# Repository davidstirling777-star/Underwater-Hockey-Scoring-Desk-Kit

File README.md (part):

# Underwater Hockey Scoring Desk Kit

A project to allow the use of a computer, modern computer languages, custom printed circuit boards and readily available Arduino or Raspberry Pi 5 hardware to make a scoring and siren system for Underwater Hockey.

**This README is the user manual for the software and hardware assembly.** It combines installation, normal operation, tournament files, two-court results synchronisation, screens, sounds and Zigbee siren setup in one place. The separate `MAINTAINERS.md` is for people modifying the Python source.

The hardware is still being developed but a working prototype has been tested and it does work well. See [Hardware assembly](#hardware-assembly) for the custom control and power PCB build and [`hardware/`](hardware/README.md) for editable KiCad sources for the five custom PCBs you will need to make the system work in totality. [Hardware setup](HARDWARE_SETUP.md) summarises current equipment and commissioning notes; use this README for the assembly wiring.

The software has an operator-facing Underwater Hockey Game Management App and player-facing and/or spectator-facing Display Window(s). The operator window defaults to opening on the **Game Variables** tab, with six other main tabs: **Scoreboard**, **Tournament List**, **Screens**, **Sounds**, **Siren Control**, and **About**.

## Contents

- [How the application works](#how-the-application-works)
- [Hardware assembly](#hardware-assembly)
- [Known working setups](#known-working-setups)
- [Windows 11 installation](#downloading-and-installing-uwh-on-windows)
- [Raspberry Pi 5 installation](#downloading-and-installing-uwh-on-a-raspberry-pi-5)
- [Game Variables tab](#game-variables-tab)
- [Tournament List tab](#tournament-list-tab)
- [Game Sequence](#game-sequence)
- [Two-court tournament results synchronisation](#two-court-tournament-results-synchronisation)
- [Screens tab](#screens-tab)
- [Sounds tab](#sounds-tab)
- [Scoreboard tab](#scoreboard-tab)
- [Other game behaviour](#other-game-behaviour)
- [Zigbee2MQTT wireless siren setup and operation](#zigbee2mqtt-wireless-siren-setup-and-operation)
- [About tab](#about-tab)
- [Other installation and packaging notes](#other-installation-and-packaging-notes)

## How the application works

UWH separates **match setup**, **live match control**, **public display**, **audio**, and **optional wireless control** so the operator can configure a game before play and then work mainly from the Scoreboard tab.

A normal operating flow is:

1. Start UWH and allow the startup self-test to complete.
2. In the **Game Variables** tab, load a preset or enter the match timings and rules.
3. If a tournament draw is being used, use the **Tournament List** tab to select the draw, starting game and any results synchronisation settings.
4. In the **Screens** tab, select the operator layout and open the required player/spectator Display Window(s). Use **Auto Detect Screens** and **Test Displays** when setting up a new computer or monitor arrangement.
5. In the **Sounds** tab, select and test the siren and pip sounds, per-file trims (to ensure the different sounds are balanced or acceptable) and siren timing.
6. If wireless Zigbee referee buttons are being used, configure and test them in the **Siren Control** tab. The wired siren supports Arduino USB and, on Pi 5, GPIO17, independently or together (see [wired siren setup](#wired-siren-on-raspberry-pi-5--gpio17-and-optional-arduino-usb)). Test each connected wired input and check its ON/OFF events in the **Siren Control → Activity Log**.
7. Use the **Scoreboard** tab during the match for goals, penalties, team time-outs and manual timer control. The player/spectator Display Window follows the live match state.
8. At the end of a tournament game, UWH saves the completed result to a separate results CSV before clearing the live match and advancing to the next selected game. If shared two-court sync is enabled, the local save happens first and network upload happens afterwards in the background (Yet to be tested).

The game clock progresses through First Half, Half Time and Second Half, with optional Overtime and Sudden Death when enabled. The detailed sequence and the special rules for goals recorded during breaks are described later in this manual.

## Hardware assembly

The [wireless siren enclosure guide](hardware/Enclosures/UWH_Siren/README.md) includes the printable parts and a photograph of an early working unit. Working units were constructed using grey PLA filament.

The editable KiCad projects and shared libraries are in [`hardware/`](hardware/README.md). These are development hardware sources, not a claim of completed production or thermal certification. The control and power boards as designed for **1 oz copper** as this seems to be significantly cheaper than 2 oz.

The DC-DC PDMs are populated by the PCB manufacturer as they use tiny SMD components, but unless you are will to pay for them to fit the pin header and viable resistor, you will have to solder them yourself.  I could not bring myself to pay the extra.

### Fit only the PDMs you need

**Only fit DC-DC PDM boards for loads that this assembly will power.** The minimum configuration uses **one PDM: the audio supply at power J15**, for a system with the power board, audio board and wired siren. The control circuit receives backed 24 V separately through power J11 → control J21; it does not need another PDM.

- If you supply your own computer instead of the onboard Raspberry Pi 5, omit the Pi PDM at **J18** and its Pi power harness. Use the external computer's audio output (via a 3.5 mm male to male cable between the computer audio socket and the Pool Audio Board 3.5 mm jack) and the Arduino USB pathway for the wired siren.
- If you are going to use the monitors own external power supplies, omit their screen PDMs at **J2/J5/J7/J9** and the corresponding screen-power leads. Fit only as many screen PDMs as there are monitors powered by this assembly.
- Fit the Raspberry Pi PDM only when powering the onboard Raspberry Pi and fit the audio PDM in every configuration described here. Unused PDM positions can remain empty.

### Board stack and assembly order

1. Open each `.kicad_pro` from KiCad's project manager. Install the standard KiCad libraries; the supplied project library tables locate the shared UWH libraries. Refill copper zones and run ERC/DRC before fabrication.
2. Assemble and inspect the power board, DC-DC PDMs and OR-ing board first. Fit the OR-ing module to **power J16**, matching numbered pins and the pin-1 marks; its two-row connector can otherwise be reversed. The supplied 2×5 assignment is SELV on pins 1–2, GND on 3–4 and 7–8, backed output on 5–6, and battery on 9–10. SELV feeds the PDMs controller (a LTC4418) pin V1 and remains the preferred source, even when the battery voltage is higher.
3. Fit only the required PDMs: screen supplies at **J2/J5/J7/J9**, the audio supply at **J15**, and the optional Pi supply at **J18**. Use **DC-DC PDM-Audio Rev D or later for the Pi supply** as eariler versions (which are opaque to you) could not get down to 5V1 required to the Raspberry Pi. **Set and measure outputs** with a multimeter before connecting loads: **19 V** for the specified screens, **16 V nominal and never above 18 V** for audio, and **5.1 V** for the Pi. Verify against each actual load's rating if you can.
4. Fit the components to the Control Board. Fit **both control-board optocouplers U1 and U2**, even if only one controller is used: their input LEDs are in series. Set JP1 **1–2 for Nano ESP32 (3.3 V)** or **2–3 for Nano Every (5 V)** before powering the Arduino. The Pi has its own 3.3 V pull-up through R13.
5. Fit the components to the audio board and the controller hardware required for your configuration: the Pi 5 stack (recommended Pimoroni NVMe Base (you can use a MicroSD at your **increased** risk), active cooler and DAC+), the Arduino, or both, on the upper assembly. Use the matching audio mounting holes.  Do not populate the **audio J5** or **control J10** header unless you are changing the board design. Audio power arrives separately by two wires at audio J19; the mating J5/J10 header still carries the same audio supply and GND, so it is not an electrically isolated mounting connector. So don't fit them.
6. Make the wire harnesses below, check polarity and continuity with power removed, then energise and test one load at a time. Do not connect another USB-C power supply to a Pi already powered through its GPIO header.
7. Mount the **control board above the power board using 30 mm standoffs** at the matching mounting holes. Support the boards without bending them; check screw length and clearance from copper, component leads and the underside of daughterboards. Keep the lower board's terminal-access edge accessible.

### Supply location and wiring sizes

**Suggested 24 V SELV PSU: Mean Well XDR-480E-24.** This model has been tested successfully with the UWH unit and has ample power headroom for the tested configuration.

Locate the **24 V SELV PSU near the 230 V power outlet**, and run several metres of twinned **4 mm² finely multistranded copper cable (approximately AWG 11)**, for 24 V positive and GND, from the PSU to the UWH siren hardware. Check the loaded supply voltage using the procedure below. Keep mains connections at the PSU end. **Containment of the boards to IPX5 is a minimum expectation.**

**24 V supply cable acceptance check:** use **24.0 V nominal at the PSU** and a recommended **maximum 1.0 V drop** from the PSU's DC output terminals to power-board J1 at the highest intended simultaneous load. This is a commissioning target for the supply wiring, **not a verified absolute undervoltage limit for the boards**.

1. With power off, disconnect the backup battery for this test so it cannot mask a weak SELV supply. Connect the equipment that this installation will actually power.
2. Run the connected screens at their highest intended brightness, exercise the computer, and sound the siren at its intended maximum operating level. Use this simultaneous operating load rather than an idle measurement.
3. Set the multimeter to **DC volts**. Measure across the PSU's accessible **+V and −V DC terminals** and record `V_PSU`. At the same steady load, measure across power-board **J1 pin 1 (+24 V) and pin 2 (GND)** and record `V_J1`. Measure only the low-voltage DC side; keep clear of the mains terminals.
4. Calculate **voltage drop = V_PSU − V_J1**. This difference already includes the positive wire, return wire and their connections; do not double it. With **24.0 V measured at the PSU**, the target is **at least 23.0 V at J1**. For example, 24.0 V at the PSU and 23.4 V at J1 gives a **0.6 V drop: pass**. A reading of 22.7 V gives **1.3 V: investigate and correct**.
5. If the PSU itself sags appreciably below its nominal 24 V, investigate its load, adjustment and temperature/derating first. If the cable drop exceeds 1.0 V, power off and inspect the ferrules, terminal tightness and connections; then increase conductor cross-sectional area using compatible, rated terminations. Do not remove strands to fit a terminal or raise the PSU voltage simply to hide cable loss. Repeat the loaded test after correcting it.
6. Confirm that the PDM outputs remain at their required voltages and that startup/siren operation causes no resets, screen blanking or unintended battery takeover. A multimeter's steady reading does not rule out brief dips; investigate any such symptoms even if the steady cable-drop test passes. Reconnect the battery with power off, then test backup operation separately.

Power-board **J1 is Phoenix Contact 1714971**. **4 mm² finely multistranded cable fits the terminals with a bootlace ferrule formed using a ferrule crimper**. Phoenix Contact publishes a **4 mm² maximum for flexible conductors, including ferruled conductors**. Do not trim away strands. Check the actual PSU terminal rating separately. Protect the long cable at its source as appropriate to the cable and PSU; the board fuse cannot protect a short upstream of itself.

Use flexible copper for internal harnesses. The following starting sizes assume maximum internal runs of **up to 250 mm one way**, Use terminations rated for the selected conductor and current. The TB007-508 terminals are specified for up to **2.5 mm²**; GPIO crimp contacts require their own wire-size check.

| Connection | Pin-to-pin wiring | Suggested conductor area, each wire |
|---|---|---|
| PSU to power board | J1 **1 = +24 V**, **2 = GND** | **4 mm² (approx. AWG 11)** |
| 24 V battery to power board | J14 **1 = battery +**, **2 = GND** | **2.5 mm² (approx. AWG 14)**; battery-source protection close to the battery |
| Power board to control board | J11 **1 → J21.1**, **2 → J21.2**: backed 24 V / GND | **0.5 mm² (approx. AWG 20)** for the control circuit only |
| Power board to audio board | J10 **1 → audio J19.1**, **2 → audio J19.2**: audio supply / GND | **1.0 mm² (approx. AWG 17)** |
| Power board to Pi power harness | J17 **1 = +5.1 V**, **2 = GND** | **1.5 mm² (approx. AWG 15)** trunk for each polarity |
| Pi harness branches | +5.1 V to physical **2 and 4**; GND to physical **6 and 9** | Two short **0.5 mm² (approx. AWG 20)** branches per polarity, with suitable current-rated contacts |
| Pi siren signal | Control J19 **1 → Pi physical 11 (BCM GPIO17)** | **0.25 mm² (approx. AWG 24)** |
| Pi pull-up supply | Pi physical **1 (3.3 V) → control J19.2** | **0.25 mm² (approx. AWG 24)** |
| Remote normally open siren button | Across control **J20 pins 1 and 2** | In-use cable: **30 metres of Cat 6a Ethernet patch cable**, plugs cut off, with **four conductors connected in parallel for each leg**, using all eight conductors |

For the remote button cable, join the same group of four conductors together at **both ends** of each leg. Connect one group between **J20 pin 1** and one button terminal, and the other group between **J20 pin 2** and the other button terminal. The normally open button closes the loop when pressed. This cable is used only as button wiring, not as an Ethernet connection.

Wind the 30 metre button cable onto a **spearfishing float-line winder** for tidy storage and easy deployment. The example below is the type used in this setup.

*Example line winder. Product photo: Ocean Hunter.*

Split the Pi power trunk using a rated splice/distribution connection; do not try to force the trunk wire into a small GPIO contact. Use both listed 5 V contacts and both ground contacts. With the DAC+ installed, use a suitable pass-through header/interposer rather than disturbing the HAT connections. An example cable connector is the **Harwin M20-1070600**, a **2×6-position, 2.54 mm female crimp housing**, fitted with separately supplied **M20-1180042** contacts. It can connect the harness to accessible mating pins covering Pi physical pins **1–12**, which include all the power, ground, 3.3 V and GPIO17 connections listed above. The housing is not itself a pass-through interposer: confirm mating-pin length, clearance and pin-1 orientation with the DAC+ fitted, and leave unused positions unwired. The M20-1180042 contacts accept **0.05–0.33 mm² (30–22 AWG)** wire, so the table's **0.5 mm² (approximately AWG 20)** power branches cannot be crimped directly into them. For this connector, use short **0.33 mm² (22 AWG)** power tails from rated splices, retaining both 5 V and both GND contacts, and verify voltage drop and temperature at the intended load. Measure 5 V at the Pi under load; do not compensate for excessive cable loss by raising the PDM above 5.1 V.

**Control J19 pin 2 is 3.3 V, not GND.** J20 is a button-loop connection, not a positive/GND supply connector. Keep these distinct from the power terminals' pin-1-positive/pin-2-GND convention. The boards share GND; the optocouplers separate the controller signal voltages but do not provide whole-system galvanic isolation.

Screen outputs are power **J3 = screen 1**, **J4 = screen 2**, **J6 = screen 3**, and **J8 = screen 4**, with positive on pin 1 and GND on pin 2. Use **1.0 mm² (approx. AWG 17)** for short screen-power leads, increasing area as needed for external cable length. Only **screen 1**, audio, Pi and the control supply are backed up by the battery via the OR-ing board; screens 2–4 use the SELV supply directly through their PDMs.

### DAC+ audio cable and volume limit

Use a straight four-conductor cable from DAC+ P6 to audio J6. Short **0.25 mm² (approx. AWG 24)** conductors are suitable; keep the audio cable away from PDM switching components and power wiring.

| DAC+ P6 | Audio J6 | Signal / audio-board destination |
|---|---|---|
| 1 | 1 | Left audio — J1 tip / R2 pad 1 |
| 2 | 2 | Ground |
| 3 | 3 | Right audio — J1 ring / R1 pad 1 |
| 4 | 4 | Ground |

For the tested **DAC+ (PCB version 003R5)**, **YOU MUST** insert an **unwired 3.5 mm plug in the DAC+ socket** to operate headphone detect. Leave **P6 pin 5 externally unconnected**: measurements show that without a plug it is directly connected to 3.3 V, so **do not bridge it to pin 4/GND**. Use one audio source at a time.

RV5 sets the maximum WATER-zone level. Looking at its adjustment screw from above, turn **anticlockwise to lower the maximum volume**. The Bourns 3296W-1-502LF has approximately 25 turns of effective adjustment and an idling wiper at the endpoints, not a hard rotational stop. Start with a low limit and set the operating level deliberately. Follow the audio schematic's two-transformer underwater-speaker wiring. Neither side of a BTL amplifier output may be connected to GND.

### Fuses and hot-climate operation

Keep the current **5 A recommendation** for power-board **F2 (battery)**, **F3 (SELV feed into the OR-ing path)** and audio-board **F2**. A **6 A fuse may need to be considered for hot climates**, subject to availability of a correctly rated part and verification of the protected wiring, connector, MOSFET and PCB paths. This is a conditional engineering review, not an instruction to increase a fuse merely because it opens.

The battery backed up load budget is **55 W screen + 30 W audio + 19.8 W Pi stack = 104.8 W**. At an assumed 90% conversion efficiency that is approximately **4.85 A at 24 V** or **5.29 A at 22 V**, before startup transients and small auxiliary loads. Retaining 5 A therefore requires checking actual simultaneous load, startup and hot-enclosure behaviour; it is not a guarantee of continuous operation at all nameplate maxima.

The separate **20 A main SELV fuse** has alternative MINI **F1 / Keystone 3568** and MAXI **F4 / Keystone 3555-2** positions. **Fit only one of F1 and F4.** The **Keystone MAXI fuse holder may need to be used in hot climates because of derating in the MINI fuse and holder**. This alternative applies to the main input fuse; it does not make the 5 A branch positions MAXI-compatible. Check both fuse and holder derating at the actual internal temperature. Record the actual fuse MPN separately from its holder MPN.

### First power-up checks

Before fitting the Pi or connecting speakers, verify each PDM's voltage and polarity. Confirm SELV is selected with both supplies present, then test battery takeover and return to SELV under the intended backed load. Check for Pi undervoltage or resets and measure connector, fuse-holder and narrow-trace temperatures during a sustained-load test. Test GPIO17 and optional Arduino USB press/release events separately and together in **Siren Control → Activity Log**. GPIO17 uses the external R13 pull-up, with internal pulls disabled; LOW means pressed. See [wired siren setup](#wired-siren-on-raspberry-pi-5--gpio17-and-optional-arduino-usb) for software behaviour.

Component references: [Phoenix 1714971](https://www.phoenixcontact.com/en-us/products/1714971), [Same Sky TB007-508 datasheet](https://www.sameskydevices.com/product/resource/tb007-508.pdf), [Littelfuse MINI fuse derating](https://www.littelfuse.com/assetdocs/littelfuse-datasheet-mini?assetguid=231dbb04-2bf5-4da4-ac3e-23aa05c4339b), [Bourns 3296 datasheet](https://www.bourns.com/data/global/pdfs/3296.pdf).

## Known working setups

## Windows 11: tested configuration (September 2026)

The Windows 11 UWH application, wired Arduino siren, Mosquitto MQTT broker and Zigbee2MQTT have been tested together with **up to three working Zigbee buttons** on one coordinator. The preferred deployment button is now the **Aqara WXKG11LM**, tested on 6 November 2026 with `single`, `double`, `hold` and `release`. Other previously tested types have limited functionality (no hold or release signals); UWH's per-button Action Mapping determines the siren response. Zigbee2MQTT was also confirmed to restart through PM2 and Windows Task Scheduler after a Windows reboot. See [the Zigbee section](#zigbee2mqtt-wireless-siren-setup-and-operation) for installation and button-mapping instructions. Do not re-pair a working button to a second coordinator just to share it with another UWH computer.

## Raspberry Pi 5: tested configuration (October 2026)

Raspberry Pi OS Desktop based on Debian 12 Bookworm (listed as Raspberry Pi OS Legacy), Python 3.11, and the X11 desktop session. Two maximised displays, mouse movement, game timers and score updates have been tested on this combination. This Raspberry Pi 5 setup has successfully run a tournament.

Why X11 matters for this application: On the tested Pi 5, moving the pointer over Game Variables checkboxes under Wayland caused GPU utilisation to reach about 98% and the mouse became jerky. A separate note: Raspberry Pi recommends Wayland generally, but X11 was demonstrably better for this GUI.

> [!IMPORTANT]
> **Recommended Pi 5 configuration:** Stay with **Bookworm + X11** until a different combination has been tested with UWH. Raspberry Pi recommends Wayland generally, but X11 was demonstrably better for the Scoring Desk Kit's GUI performance on Bookworm.

#### Select X11 on Raspberry Pi OS
1. Open Terminal and run `sudo raspi-config`.
2. Select **6 Advanced Options** → **A7 Wayland** → **W1 X11**.
3. Select Finish and reboot when prompted.
4. After reboot, run:
   ```bash
   echo $XDG_SESSION_TYPE
   ```
   It should print `x11`. If it prints `wayland`, check the selection and reboot again. To switch back later, use **W2 Labwc** in the same menu.

## Downloading and installing UWH on Windows

### Download the program
1. Open the UWH Scoring Desk Kit repository on GitHub.
2. On the right-hand side of the repository page, find **Releases**.
3. Click Releases, then select the latest release.
4. Scroll down to the **Assets** section.
5. Click the Windows ZIP file. Its name will resemble: `UnderwaterHockeyScoringDesk-v1.2.123-Windows.zip`
   (The version and build numbers will vary.)
6. The ZIP file will download to your computer, normally into your Downloads folder.

> [!IMPORTANT]
> Do not select **Source code (zip)** or use the green **Code → Download ZIP** button. Those download the Python source code, not the ready-to-run Windows application.

### Extract the program
1. Open Windows File Explorer and navigate to Downloads.
2. Right-click the downloaded ZIP file.
3. Select **Extract All...**
4. Choose a permanent folder, such as `Documents\UWH Scoring Desk`.
5. Click Extract.

The extracted folder contains `UnderwaterHockeyScoringDesk.exe`, the visible `Tournament data` and `Sounds` folders, and its supporting files. Keep these together.

### Run the application
1. Open the extracted folder.
2. Double-click `UnderwaterHockeyScoringDesk.exe`.
3. The startup self-test will run before the application opens.
4. The Game Management window will appear.
5. Use the **Screens** tab's **Display Screen Options** to open a player-facing or crowd-facing display, if required. Choose a supported Standard or Widescreen layout. Closing a Display Window with its **X** closes it and queues the closed state for the next automatic settings save (about one minute after the first change, or on normal program exit). Check your monitor assignments with **Auto Detect Screens** and **Test Displays**.

You can create a desktop shortcut by right-clicking the executable and selecting **Show more options → Send to → Desktop (create shortcut)**.

### Installing future updates

Download the newer release and extract it into a **separate folder** first. Do not overwrite a working installation without a backup.

> [!WARNING]
> **Back up `settings.json` before every update.** It includes your **Zigbee button-name list** (for example, `siren_button, siren_button_2, siren_button_3`), MQTT settings, sound preferences, screen layout and the remembered Display Window open/closed state. Back up tournament CSVs, custom sounds in the app-level `Sounds` folder, and game logs too. Replacing UWH's settings can lose button names **or action mappings**, even though the buttons remain paired to Zigbee2MQTT.

After updating, confirm the **Siren Control → Button Device Names** field and test every configured button and its action mapping before using the system at a match. The lower-right corner of the **Game Variables** panel shows the running UWH version so you can confirm which download is actually open. Windows and Raspberry Pi 5 release builds show the same `1.2.<build>` number used in their release ZIP names; source installations show a source-build identifier. Do not blindly replace a new-format `settings.json` with a very old version; compare and carry forward your customised values where the format has changed. Zigbee2MQTT has a **separate** `data/` directory that should be backed up before Zigbee2MQTT updates; see [the Zigbee section](#zigbee2mqtt-wireless-siren-setup-and-operation).

## Downloading and installing UWH on a Raspberry Pi 5

The normal Raspberry Pi 5 installation now uses the ready-to-run **Linux ARM64 release ZIP** produced by GitHub Actions. A keyboard, mouse and 64-bit Raspberry Pi OS Desktop are needed; the Lite edition does not include the graphical desktop. The release bundle includes the Python runtime and UWH Python dependencies, so ordinary users do **not** need to create a virtual environment or run `pip install`.

### Raspberry Pi 5 power supply configurations

Raspberry Pi 5 can be powered in several ways, but the power source affects how much current the firmware makes available to the board and to USB peripherals. Raspberry Pi recommends a **5 V / 5 A** supply for full capability. A good **5 V / 3 A** supply can run a Pi 5, but the total current available to downstream USB peripherals is normally limited to **600 mA** instead of **1.6 A**.

| Power arrangement | Pi 5 behaviour | Required configuration |
|---|---|---|
| **UWH Scoring Desk production power board — 5.1 V / at least 5 A through the GPIO header** | No USB-C Power Delivery negotiation occurs. The motherboard provides the high-current 5 V rail directly. | **Set `PSU_MAX_CURRENT=5000` in the Pi 5 bootloader EEPROM.** |
| **Official Raspberry Pi 27 W USB-C supply, or another compatible USB-PD source that negotiates 5 V / 5 A** | The Pi detects the 5 A supply through USB-PD and automatically enables the higher power budget. | No `PSU_MAX_CURRENT` override is normally required. |
| **Good-quality 5 V / 3 A USB-C supply** | The Pi 5 can operate, but downstream USB power is normally limited to 600 mA. | Do **not** claim 5 A with `PSU_MAX_CURRENT=5000` unless the supply and complete power path really can provide it. |
| **Other verified 5 V / 5 A non-PD supply or bench supply connected through GPIO** | Electrically similar to the UWH GPIO-powered case: there is no USB-PD negotiation to report the available current. | `PSU_MAX_CURRENT=5000` may be used only when the source, wiring and connectors are genuinely capable of supplying 5 A. |

#### UWH Scoring Desk production hardware

> [!IMPORTANT]
> **The UWH Scoring Desk power board provides the Raspberry Pi 5 with a regulated 5.1 V supply capable of at least 5 A through the GPIO header. The dedicated PDM-Audio DC-DC supply uses the LMQ61460 regulator. The regulator specifies 3.5–7 ms from its first switching pulse to 90% of the selected output voltage, with a typical 0.7 ms enable-to-first-switching-pulse delay. This keeps the regulator's designed start-up to near operating voltage below 10 ms. The assembled production board should still be checked under load during hardware validation.**

The production power board feeds the Pi 5 through the **5 V GPIO power pins rather than through USB-C**. This deliberately bypasses USB-C Power Delivery negotiation. Most users are expected to provide their own Raspberry Pi 5, so each Pi powered by the production power board must have its bootloader configured to recognise the available **5000 mA** supply.

For the UWH power board, edit the Pi 5 bootloader EEPROM configuration:

```bash
sudo rpi-eeprom-config --edit
```

Add or change:

```text
PSU_MAX_CURRENT=5000
```

Save the configuration and reboot:

```bash
sudo reboot
```

After rebooting, verify the setting:

```bash
rpi-eeprom-config | grep PSU_MAX_CURRENT
```

The result should include:

```text
PSU_MAX_CURRENT=5000
```

`PSU_MAX_CURRENT=5000` tells the Pi 5 firmware to **skip USB Power Delivery negotiation and assume that a 5 A source is available**. It does not increase the capability of the power supply itself. On the UWH power board this is appropriate because the dedicated PDM-Audio supply and its power path are designed for the Pi 5 load.

Raspberry Pi also provides a `usb_max_current_enable=1` setting that raises the USB peripheral limit from 600 mA to 1.6 A. **It does not need to be added separately for the UWH power board:** Raspberry Pi documents that this higher USB-current setting is enabled automatically when `PSU_MAX_CURRENT=5000` is set.

> [!CAUTION]
> **Do not use `PSU_MAX_CURRENT=5000` merely to remove a low-power warning.** Only use it when the complete 5 V supply path is genuinely capable of supplying 5 A. If a Pi 5 is removed from the UWH power board and later used with a lower-current supply, review or remove this EEPROM override. Also avoid connecting a second USB-C power supply while the Pi is already being powered from the UWH power board's GPIO 5 V rail.

#### If the Pi 5 is powered through USB-C instead

A Pi 5 supplied from an official Raspberry Pi 27 W USB-C supply negotiates **5 V / 5 A** using USB Power Delivery, so the firmware knows that the higher current is available and no UWH-specific EEPROM override is required.

A Pi 5 can also run from a suitable **5 V / 3 A** USB-C source. In that configuration Raspberry Pi normally restricts the total power available to downstream USB devices to **600 mA**. With a recognised 5 V / 5 A source—or with the UWH power board correctly configured using `PSU_MAX_CURRENT=5000`—the USB peripheral limit rises to **1.6 A**.

The production UWH power board uses GPIO power injection rather than USB-C because its dedicated regulated 5.1 V supply is already part of the scoring-desk hardware; implementing a separate USB-C 5 A source would otherwise require a suitable USB-C/USB-PD power-source arrangement.

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
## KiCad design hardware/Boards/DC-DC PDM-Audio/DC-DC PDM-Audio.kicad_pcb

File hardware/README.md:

# UWH scoring hardware

Start with [Hardware assembly in the main README](../README.md#hardware-assembly) for the Cower and Control board stack, wiring tables, power settings and commissioning checks.

Five current projects are included:

| Project folder under `Boards/` | Purpose |  Copper Weight |
|---|---|---|
| `UWH Power Board` | Lower board: fused supply inputs, PDMs and OR-ing module |  **2 oz copper on both F.Cu and B.Cu**  |
| `UWH Control Board` | Upper board: controller connections, Arduino footprint (sometimes optional) and audio/Pi mounting |  1 oz copper on both F.Cu and B.Cu  |
| `Pool_Audio_Zone` | Audio mixer, amplifier connections and speaker filters |  1 oz copper on both F.Cu and B.Cu  |
| `OR-ing board` | LTC4418 SELV-priority / battery-backup selector |  **2 oz** copper on both F.Cu and B.Cu  |
| `DC-DC PDM-Audio` | Adjustable DC-DC supply module; verify revision/output for each load |  **2 oz** copper on both F.Cu and B.Cu  |

Open the `.kicad_pro` file in the chosen folder from KiCad's project manager. Use KiCad 10 or a newer compatible version, with the standard symbol, footprint and 3D-model libraries installed. Keep the directory structure intact. Project-local library tables point to `../../Libraries`.

`Libraries/UWH.kicad_sym`, `Libraries/UWH.pretty`, `Libraries/Stack_Template.pretty` and `Libraries/UWH.3dshapes` contain the shared assets. The OR-ing project also registers its supplied local LTC4418 symbol library. Custom library definitions are supplied; embedded board/schematic instances may contain deliberate local edits. Review differences before updating existing instances from a library.

Generate fresh manufacturing files from the chosen project after review and ERC/DRC; this import is not manufacturing approval nor a guarentee of perfection.

Some unused legacy library footprints refer to optional models not supplied (notably the WE-XHMI-6030P). These do not affect the five boards' custom model resolution. Carrier/stack STEP models are mechanical references and may not reflect every subsequent routing or silkscreen change.

Before ordering parts, check actual component MPNs, separate fuse/holder BOM entries, the JP1 header and shunt, and mating cable housings/contacts. Run KiCad ERC and DRC with zones refilled. Test the completed assembly's load, temperature, startup and supply changeover behaviour.

## Printed siren button enclosure

The [UWH siren enclosure](Enclosures/UWH_Siren/README.md) contains the pipe adaptor and removable cup STEP files, assembly guidance and an early working-unit photo. Working units were constructed using grey PLA filament.

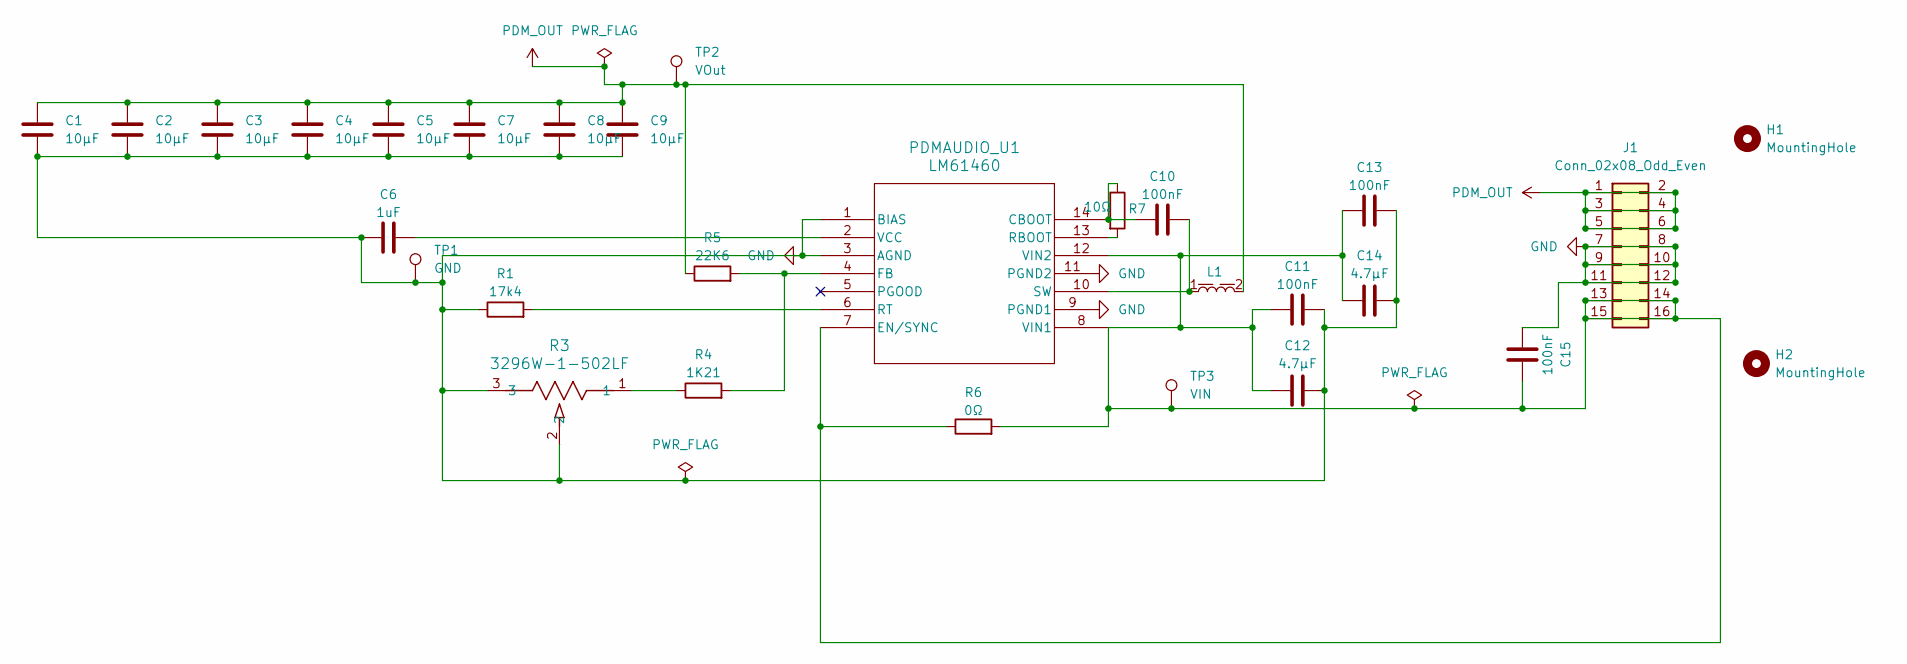
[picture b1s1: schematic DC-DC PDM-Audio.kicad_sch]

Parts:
C1, C2, C3, C4, C5, C7, C8, C9: 10µF; C_1210_3225Metric; MPN GRJ32ER71H106KE11K
C6: 1uF; C_0603_1608Metric; MPN GCM188R71C105KA64D
C10: 100nF; C_0805_2012Metric; MPN GCM21BR71H104KA37L
C11, C13, C15: 100nF; C_0603_1608Metric; MPN GCM188R71H104KA57D
C12, C14: 4.7µF; C_1206_3216Metric; MPN GRM31CR71H475KA12L
H1, H2: MountingHole; MountingHole_3.2mm_M3
J1: Conn_02x08_Odd_Even; PinHeader_2x08_P2.54mm_Vertical; MPN TSW-108-07-F-D
L1: 744393665100; Wurth_744393665100_WE-XHMI_1060; MPN 744393665100
PDMAUDIO_U1: LM61460; VQFN-HR14_RJR_TEX; MPN LMQ61460AFSQRJRRQ1
R1: 17k4; R_0603_1608Metric; MPN RC0603FR-0717K4L
R3: 3296W-1-502LF; Potentiometer_Bourns_3296W_Vertical; MPN 3296W-1-502LF
R4: 1K21; R_0603_1608Metric_Pad0.98x0.95mm_HandSolder; MPN RT0603BRE071K21L
R5: 22K6; R_0603_1608Metric_Pad0.98x0.95mm_HandSolder; MPN RT0603BRD0722K6L
R6: 0Ω; R_0603_1608Metric; MPN RC0603JR-070RL
R7: 10Ω; R_0603_1608Metric; MPN AC0603FR-0710RL
TP1: GND; TestPoint_Pad_D1.5mm
TP2: VOut; TestPoint_Pad_D1.5mm
TP3: VIN; TestPoint_Pad_D1.5mm

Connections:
GND: C1.2, C2.2, C3.2, C4.2, C5.2, C6.1, C7.2, C8.2, C9.2, C11.2, C12.2, C13.2, C14.2, C15.1, J1.7, J1.8, J1.9, J1.10, J1.11, J1.12, PDMAUDIO_U1.1 (BIAS), PDMAUDIO_U1.3 (AGND), PDMAUDIO_U1.9 (PGND1), PDMAUDIO_U1.11 (PGND2), R1.1, R3.2, R3.3, TP1.1 (1_1)
unnamed: C11.1, C12.1, C13.1, C14.1, C15.2, J1.13, J1.14, J1.15, J1.16, PDMAUDIO_U1.7 (EN/SYNC), PDMAUDIO_U1.8 (VIN1), PDMAUDIO_U1.12 (VIN2), R6.1, R6.2, TP3.1 (1_1)
unnamed: C10.1, PDMAUDIO_U1.14 (CBOOT), R7.1
unnamed: PDMAUDIO_U1.4 (FB), R4.2, R5.2
unnamed: PDMAUDIO_U1.13 (RBOOT), R7.2
unnamed: PDMAUDIO_U1.6 (RT), R1.2
unnamed: C10.2, L1.1, PDMAUDIO_U1.10 (SW)
unnamed: C6.2, PDMAUDIO_U1.2 (VCC)
unnamed: R3.1, R4.1
PDM_OUT: C1.1, C2.1, C3.1, C4.1, C5.1, C7.1, C8.1, C9.1, J1.1, J1.2, J1.3, J1.4, J1.5, J1.6, L1.2, R5.1, TP2.1 (1_1)

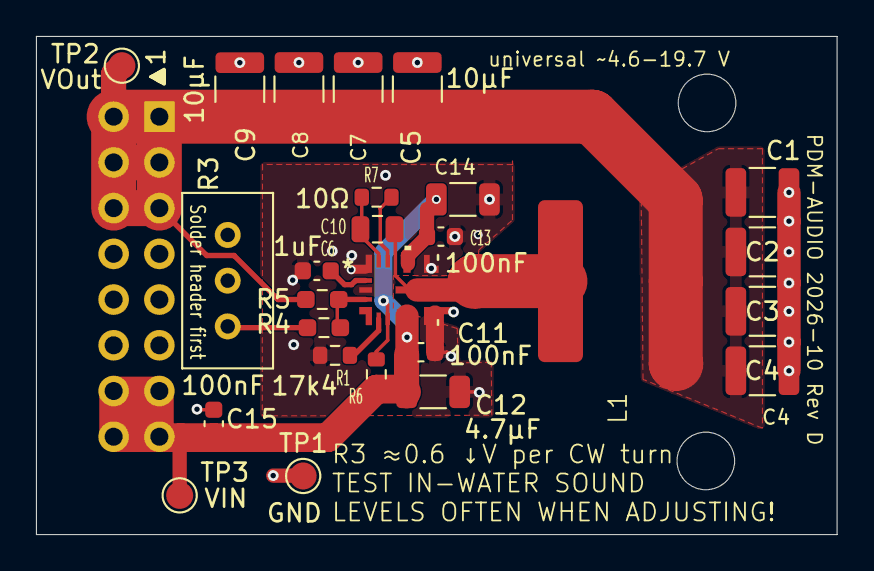
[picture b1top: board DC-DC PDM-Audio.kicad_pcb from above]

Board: 2 copper layers, 44.5 x 27.7 mm, 29 parts (1 on the bottom side), 10 nets.

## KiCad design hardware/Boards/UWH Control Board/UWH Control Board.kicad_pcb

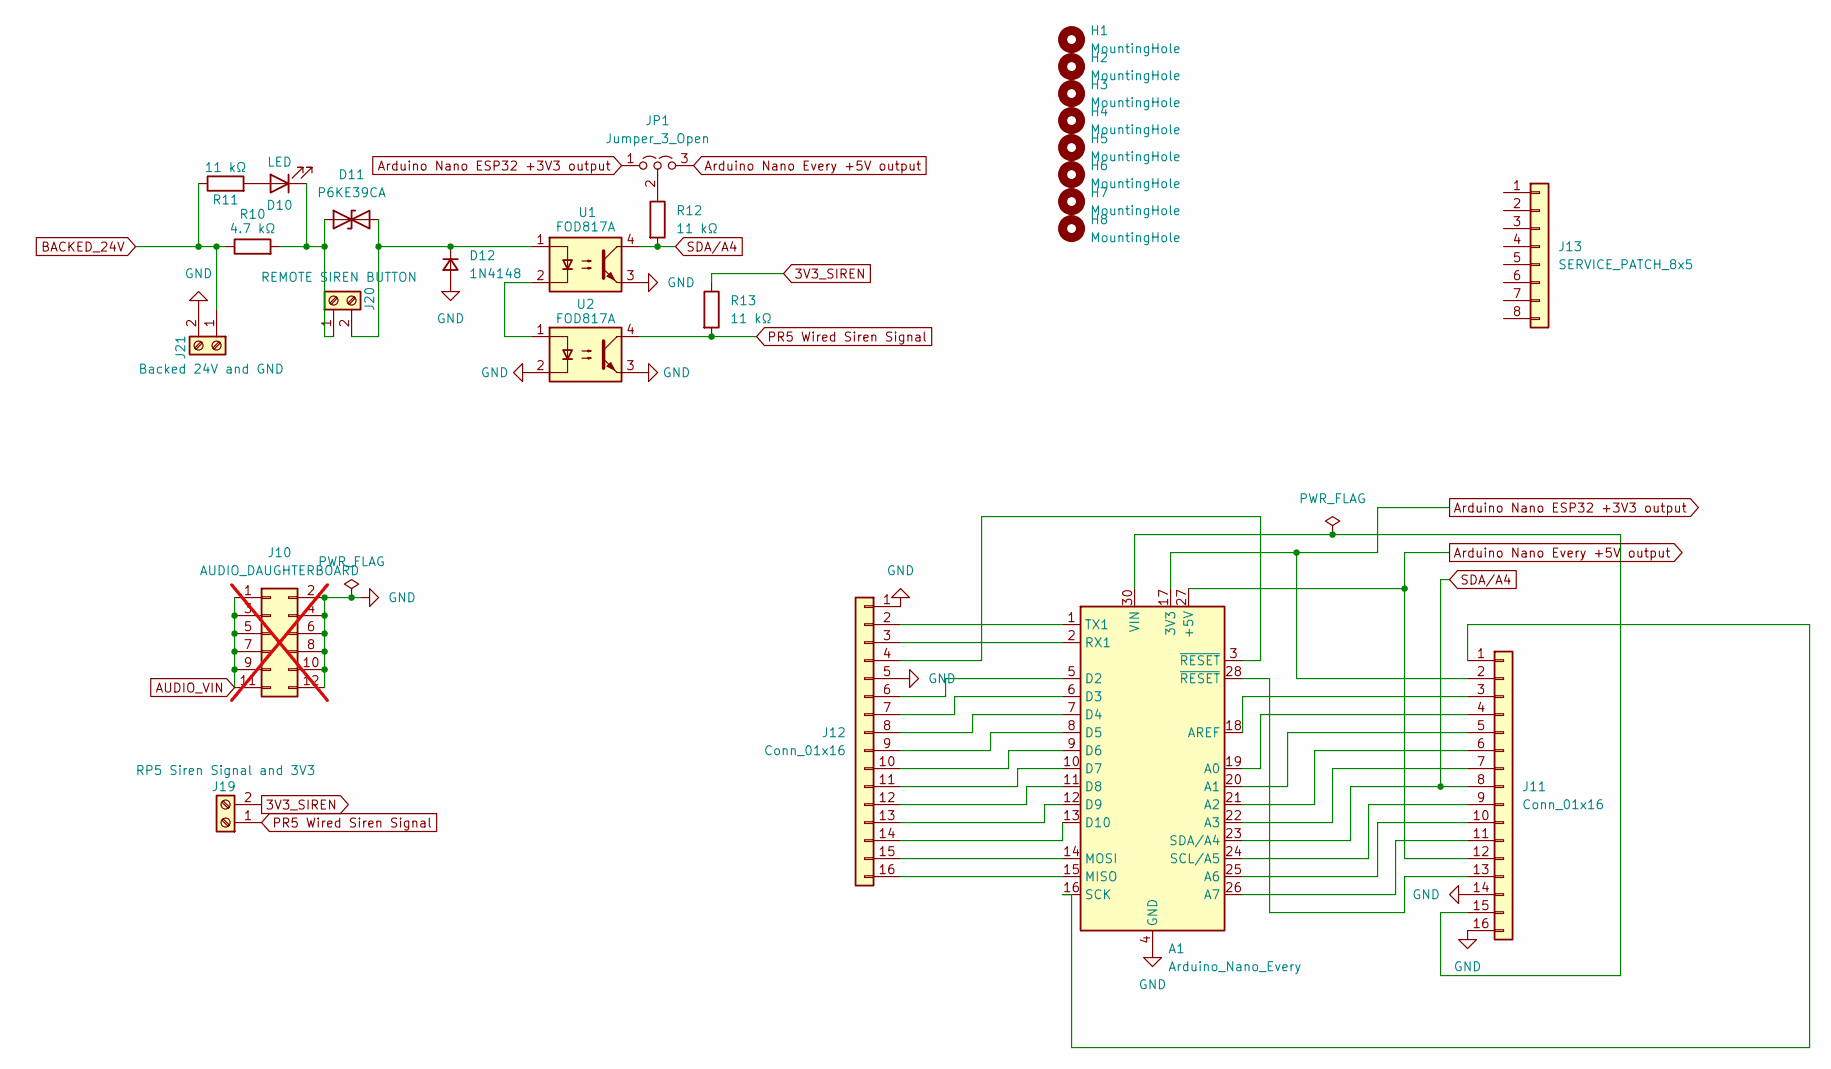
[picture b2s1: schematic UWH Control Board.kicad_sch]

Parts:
A1: Arduino_Nano_Every; Arduino_Nano
D10: LED; LED_D3.0mm; MPN WP710A10LCGDK
D11: P6KE39CA; D_DO-15_P12.70mm_Horizontal; MPN P6KE39CA
D12: 1N4148; D_DO-35_SOD27_P7.62mm_Horizontal; MPN 1N4148
H1, H2, H3, H4, H5, H6, H7, H8: MountingHole; MountingHole_3.2mm_M3_Clearance7.2mm
J10: AUDIO_DAUGHTERBOARD; UWH_Audio_Daughterboard_2x6; MPN SSW-106-02-G-D; not fitted
J11, J12: Conn_01x16; PHOENIX_1984756; MPN 1984756
J13: SERVICE_PATCH_8x5; THT_Bus_8x5_2.54mm
J19: RP5 Siren Signal and 3V3; TerminalBlock_CUI_TB007-508-02_1x02_P5.08mm_Horizontal; MPN TB007-508-02BE
J20: REMOTE SIREN BUTTON; TerminalBlock_CUI_TB007-508-02_1x02_P5.08mm_Horizontal; MPN TB007-508-02BE
J21: Backed 24V and GND; TerminalBlock_CUI_TB007-508-02_1x02_P5.08mm_Horizontal; MPN TB007-508-02BE
JP1: Jumper_3_Open; PinHeader_1x03_P2.54mm_Vertical; MPN 61300311121
R10: 4.7 kΩ; R_Axial_DIN0207_L6.3mm_D2.5mm_P7.62mm_Horizontal; MPN MF0207FRE52-4K7
R11, R12, R13: 11 kΩ; R_Axial_DIN0207_L6.3mm_D2.5mm_P7.62mm_Horizontal; MPN MFR-25FRF52-11K
U1, U2: FOD817A; DIP-4_W7.62mm; MPN FOD817A

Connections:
3V3_SIREN: J19.2, R13.1
AUDIO_VIN: J10.1, J10.3, J10.5, J10.7, J10.9, J10.11
Arduino Nano ESP32 +3V3 output: A1.17 (3V3), J11.2, JP1.1 (A)
Arduino Nano Every +5V output: A1.27 (+5V), J11.12, JP1.3 (B)
BACKED_24V: J21.1, R10.1, R11.1
GND: A1.4 (GND), A1.29 (GND), D12.2 (A), J10.2, J10.4, J10.6, J10.8, J10.10, J10.12, J11.14, J11.16, J12.1, J12.5, J21.2, U1.3, U2.2, U2.3
unnamed: A1.19 (A0), J11.4
unnamed: A1.20 (A1), J11.5
unnamed: A1.21 (A2), J11.6
unnamed: A1.22 (A3), J11.7
unnamed: A1.25 (A6), J11.10
unnamed: A1.26 (A7), J11.11
unnamed: A1.18 (AREF), J11.3
unnamed: A1.5 (D2), J12.6
unnamed: A1.6 (D3), J12.7
unnamed: A1.7 (D4), J12.8
unnamed: A1.8 (D5), J12.9
unnamed: A1.9 (D6), J12.10
unnamed: A1.10 (D7), J12.11
unnamed: A1.11 (D8), J12.12
unnamed: A1.12 (D9), J12.13
unnamed: A1.13 (D10), J12.14
unnamed: A1.15 (MISO), J12.16
unnamed: A1.14 (MOSI), J12.15
unnamed: A1.2 (RX1), J12.3
unnamed: A1.16 (SCK), J11.1
unnamed: A1.24 (SCL/A5), J11.9
unnamed: A1.1 (TX1), J12.2
unnamed: A1.30 (VIN), J11.15
unnamed: D10.2 (A), R11.2
unnamed: D10.1 (K), D11.1 (A1), J20.1, R10.2
unnamed: D11.2 (A2), D12.1 (K), J20.2, U1.1
unnamed: A1.28 (~RESET), J11.13
unnamed: A1.3 (~RESET), J12.4
unnamed: JP1.2 (C), R12.1
unnamed: U1.2, U2.1
PR5 Wired Siren Signal: J19.1, R13.2, U2.4
SDA/A4: A1.23 (SDA/A4), J11.8, R12.2, U1.4

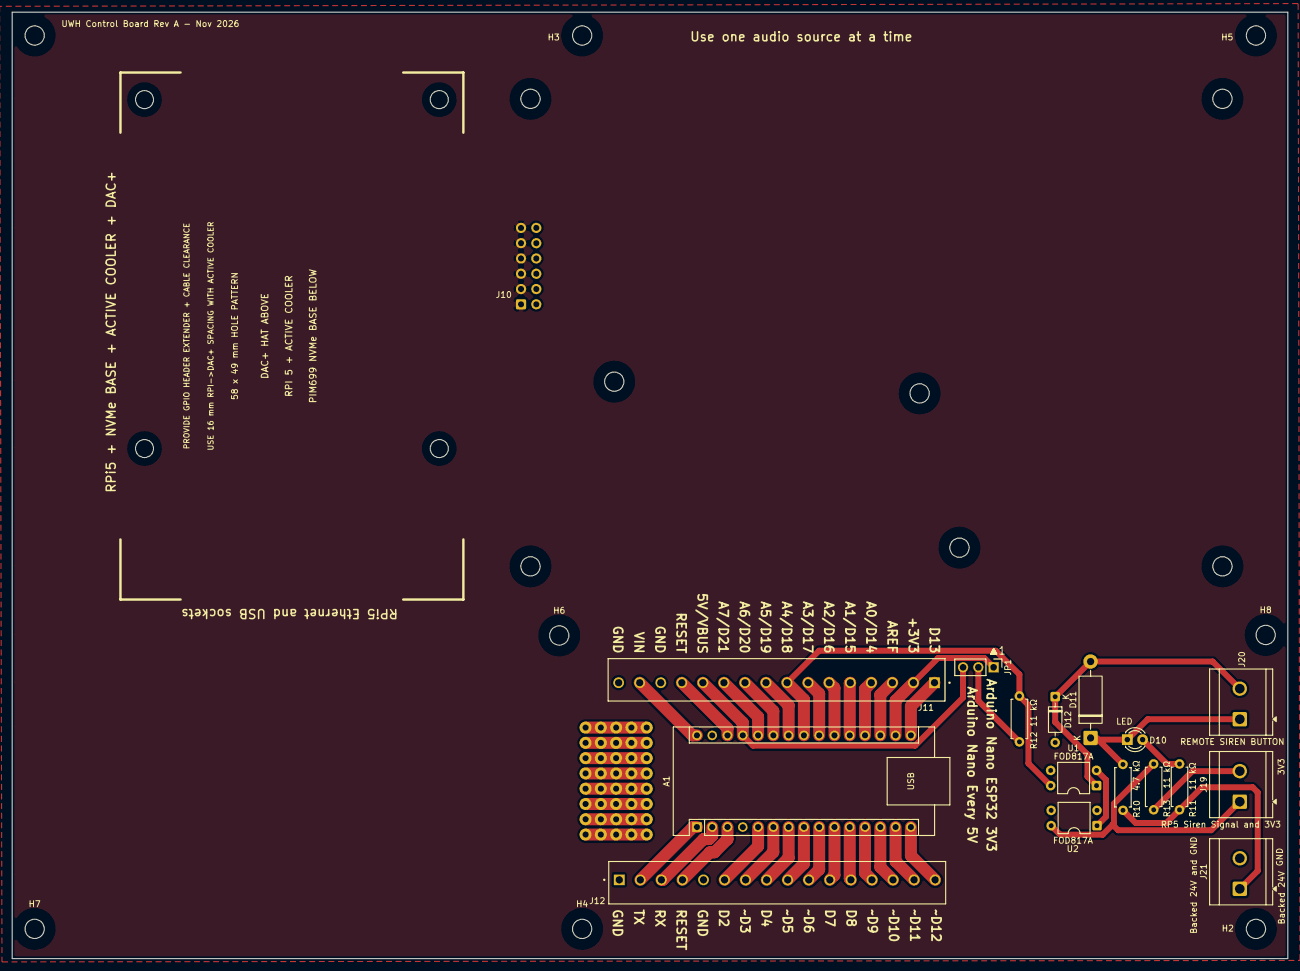
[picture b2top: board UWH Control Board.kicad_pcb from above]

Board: 2 copper layers, 212.0 x 157.3 mm, 27 parts (0 on the bottom side), 38 nets.

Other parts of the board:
RPi5 + NVMe BASE + ACTIVE COOLER + DAC+: Raspberry_Pi5_NVMeBase_DACplus_Carrier

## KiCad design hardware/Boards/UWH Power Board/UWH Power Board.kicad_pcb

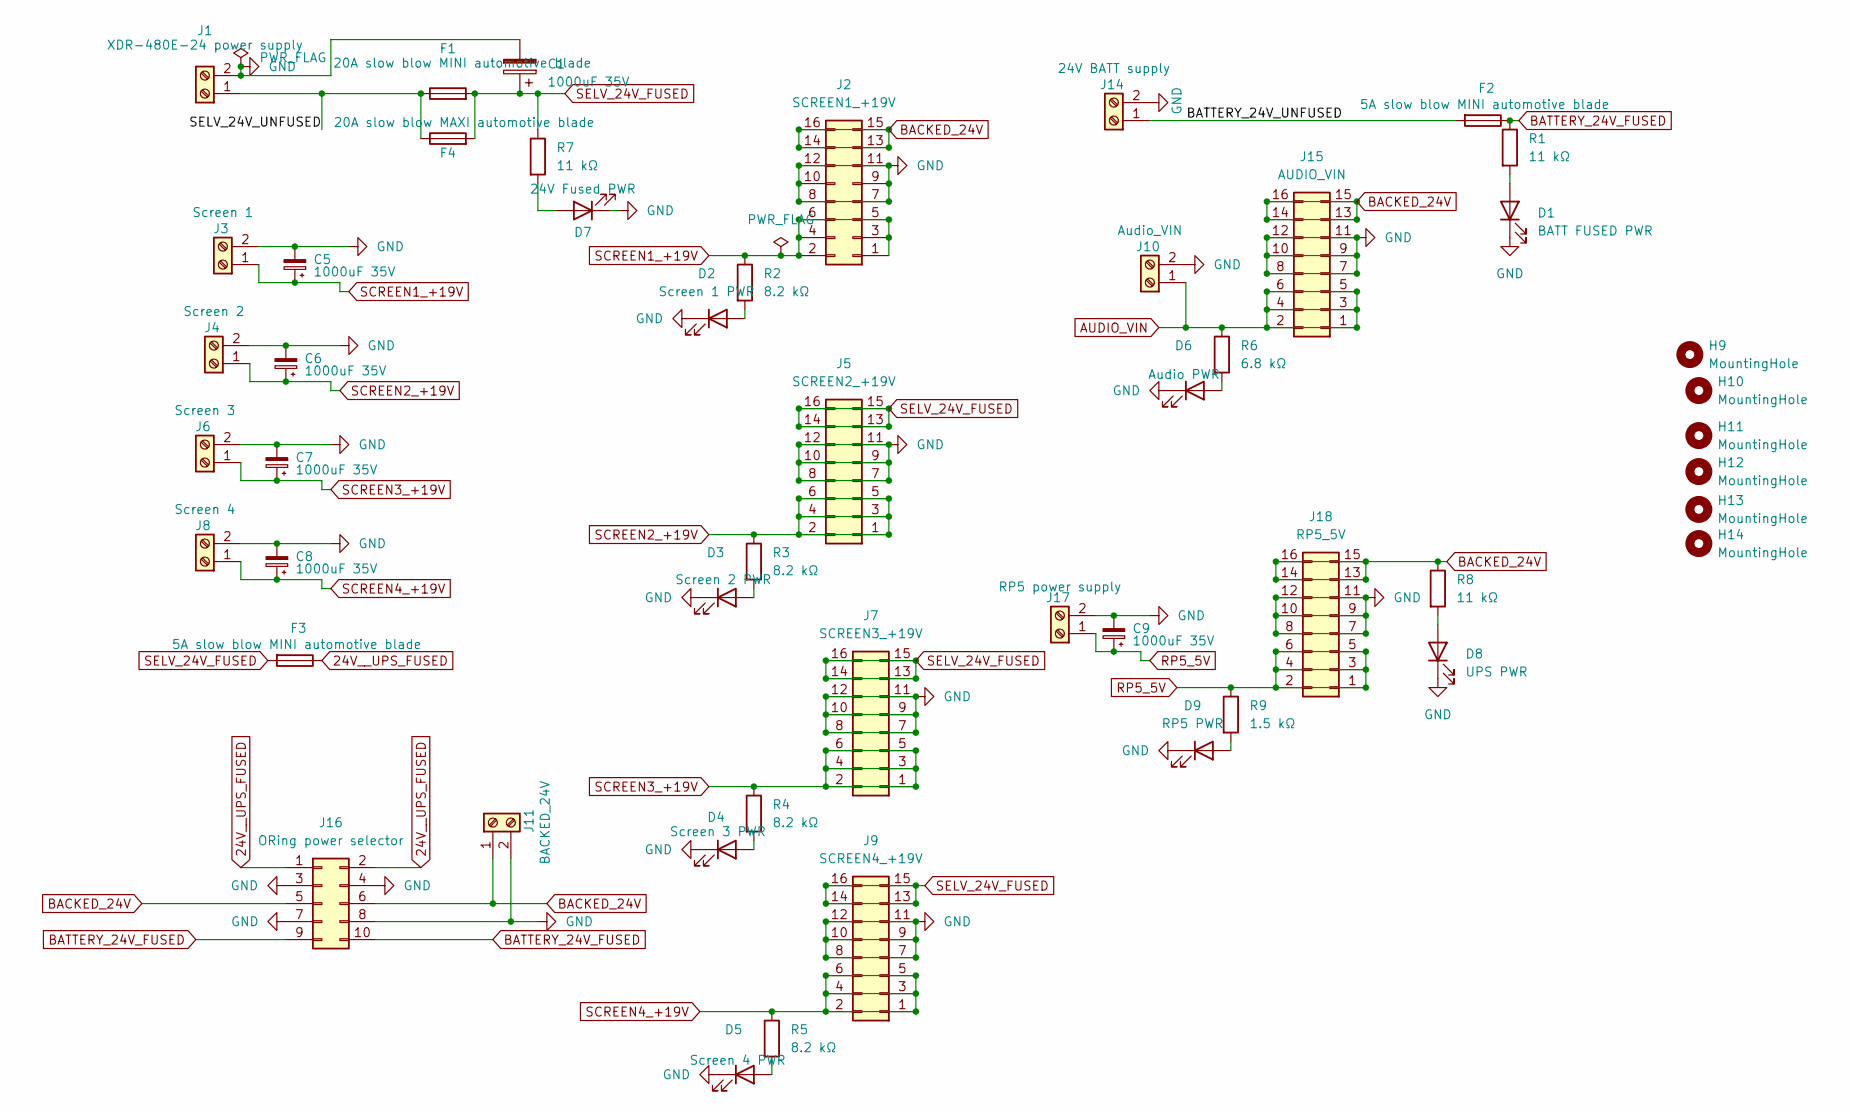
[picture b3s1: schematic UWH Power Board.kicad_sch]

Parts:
C1, C5, C6, C7, C8, C9: 1000uF 35V; CP_Radial_D12.5mm_P5.00mm; MPN 35ZLH1000MEFC12.5X20
D1: BATT FUSED PWR; LED_D3.0mm; MPN WP710A10LCGDK
D2: Screen 1 PWR; LED_D3.0mm; MPN WP710A10LCGDK
D3: Screen 2 PWR; LED_D3.0mm; MPN WP710A10LCGDK
D4: Screen 3 PWR; LED_D3.0mm; MPN WP710A10LCGDK
D5: Screen 4 PWR; LED_D3.0mm; MPN WP710A10LCGDK
D6: Audio PWR; LED_D3.0mm; MPN WP710A10LCGDK
D7: 24V Fused PWR; LED_D3.0mm; MPN WP710A10LCGDK
D8: UPS PWR; LED_D3.0mm; MPN WP710A10LCGDK
D9: RP5 PWR; LED_D3.0mm; MPN WP710A10LCGDK
F1: 20A slow blow MINI automotive blade; Fuseholder_Blade_Mini_Keystone_3568; MPN 3568
F2, F3: 5A slow blow MINI automotive blade; Fuseholder_Blade_Mini_Keystone_3568; MPN 3568
F4: 20A slow blow MAXI automotive blade; Fuseholder_Keystone_3555-2; MPN 3555-2
H9, H10, H11, H12, H13, H14: MountingHole; MountingHole_3.2mm_M3_Clearance7.2mm
J1: XDR-480E-24 power supply; CONN_1714971_PXC; MPN 1714971
J2: SCREEN1_+19V; PinSocket_2x08_P2.54mm_Vertical; MPN SSW-108-02-G-D
J3: Screen 1; TerminalBlock_CUI_TB007-508-02_1x02_P5.08mm_Horizontal; MPN TB007-508-02BE
J4: Screen 2; TerminalBlock_CUI_TB007-508-02_1x02_P5.08mm_Horizontal; MPN TB007-508-02BE
J5: SCREEN2_+19V; PinSocket_2x08_P2.54mm_Vertical; MPN SSW-108-02-G-D
J6: Screen 3; TerminalBlock_CUI_TB007-508-02_1x02_P5.08mm_Horizontal; MPN TB007-508-02BE
J7: SCREEN3_+19V; PinSocket_2x08_P2.54mm_Vertical; MPN SSW-108-02-G-D
J8: Screen 4; TerminalBlock_CUI_TB007-508-02_1x02_P5.08mm_Horizontal; MPN TB007-508-02BE
J9: SCREEN4_+19V; PinSocket_2x08_P2.54mm_Vertical; MPN SSW-108-02-G-D
J10: Audio_VIN; TerminalBlock_CUI_TB007-508-02_1x02_P5.08mm_Horizontal; MPN TB007-508-02BE
J11: BACKED_24V; TerminalBlock_CUI_TB007-508-02_1x02_P5.08mm_Horizontal; MPN TB007-508-02BE
J14: 24V BATT supply; TerminalBlock_CUI_TB007-508-02_1x02_P5.08mm_Horizontal; MPN TB007-508-02BE
J15: AUDIO_VIN; PinSocket_2x08_P2.54mm_Vertical; MPN SSW-108-02-G-D
J16: ORing power selector; ORing_Socket_SSW-105-02-G-D_v5; MPN SSW-105-02-G-D
J17: RP5 power supply; TerminalBlock_CUI_TB007-508-02_1x02_P5.08mm_Horizontal; MPN TB007-508-02BE
J18: RP5_5V; PinSocket_2x08_P2.54mm_Vertical; MPN SSW-108-02-G-D
R1, R7, R8: 11 kΩ; R_Axial_DIN0207_L6.3mm_D2.5mm_P7.62mm_Horizontal; MPN MFR-25FRF52-11K
R2, R3, R4, R5: 8.2 kΩ; R_Axial_DIN0207_L6.3mm_D2.5mm_P7.62mm_Horizontal; MPN MFR-25FRF52-8K2
R6: 6.8 kΩ; R_Axial_DIN0207_L6.3mm_D2.5mm_P7.62mm_Horizontal; MPN MFR-25FRF52-6K8
R9: 1.5 kΩ; R_Axial_DIN0207_L6.3mm_D2.5mm_P7.62mm_Horizontal; MPN MFR-25FRF52-1K5

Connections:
24V__UPS_FUSED: F3.1, J16.1, J16.2
/BATTERY_24V_UNFUSED: F2.2, J14.1
/SELV_24V_UNFUSED: F1.1, F4.1, J1.1
AUDIO_VIN: J10.1, J15.1, J15.2, J15.3, J15.4, J15.5, J15.6, R6.1
BACKED_24V: J2.13, J2.14, J2.15, J2.16, J11.1, J15.13, J15.14, J15.15, J15.16, J16.5, J16.6, J18.13, J18.14, J18.15, J18.16, R8.1
BATTERY_24V_FUSED: F2.1, J16.9, J16.10, R1.1
GND: C1.2, C5.2, C6.2, C7.2, C8.2, C9.2, D1.1 (K), D2.1 (K), D3.1 (K), D4.1 (K), D5.1 (K), D6.1 (K), D7.1 (K), D8.1 (K), D9.1 (K), J1.2, J2.7, J2.8, J2.9, J2.10, J2.11, J2.12, J3.2, J4.2, J5.7, J5.8, J5.9, J5.10, J5.11, J5.12, J6.2, J7.7, J7.8, J7.9, J7.10, J7.11, J7.12, J8.2, J9.7, J9.8, J9.9, J9.10, J9.11, J9.12, J10.2, J11.2, J14.2, J15.7, J15.8, J15.9, J15.10, J15.11, J15.12, J16.3, J16.4, J16.7, J16.8, J17.2, J18.7, J18.8, J18.9, J18.10, J18.11, J18.12
unnamed: D1.2 (A), R1.2
unnamed: D2.2 (A), R2.2
unnamed: D3.2 (A), R3.2
unnamed: D4.2 (A), R4.2
unnamed: D5.2 (A), R5.2
unnamed: D6.2 (A), R6.2
unnamed: D7.2 (A), R7.2
unnamed: D8.2 (A), R8.2
unnamed: D9.2 (A), R9.2
RP5_5V: C9.1, J17.1, J18.1, J18.2, J18.3, J18.4, J18.5, J18.6, R9.1
SCREEN1_+19V: C5.1, J2.1, J2.2, J2.3, J2.4, J2.5, J2.6, J3.1, R2.1
SCREEN2_+19V: C6.1, J4.1, J5.1, J5.2, J5.3, J5.4, J5.5, J5.6, R3.1
SCREEN3_+19V: C7.1, J6.1, J7.1, J7.2, J7.3, J7.4, J7.5, J7.6, R4.1
SCREEN4_+19V: C8.1, J8.1, J9.1, J9.2, J9.3, J9.4, J9.5, J9.6, R5.1
SELV_24V_FUSED: C1.1, F1.2, F3.2, F4.2, J5.13, J5.14, J5.15, J5.16, J7.13, J7.14, J7.15, J7.16, J9.13, J9.14, J9.15, J9.16, R7.1

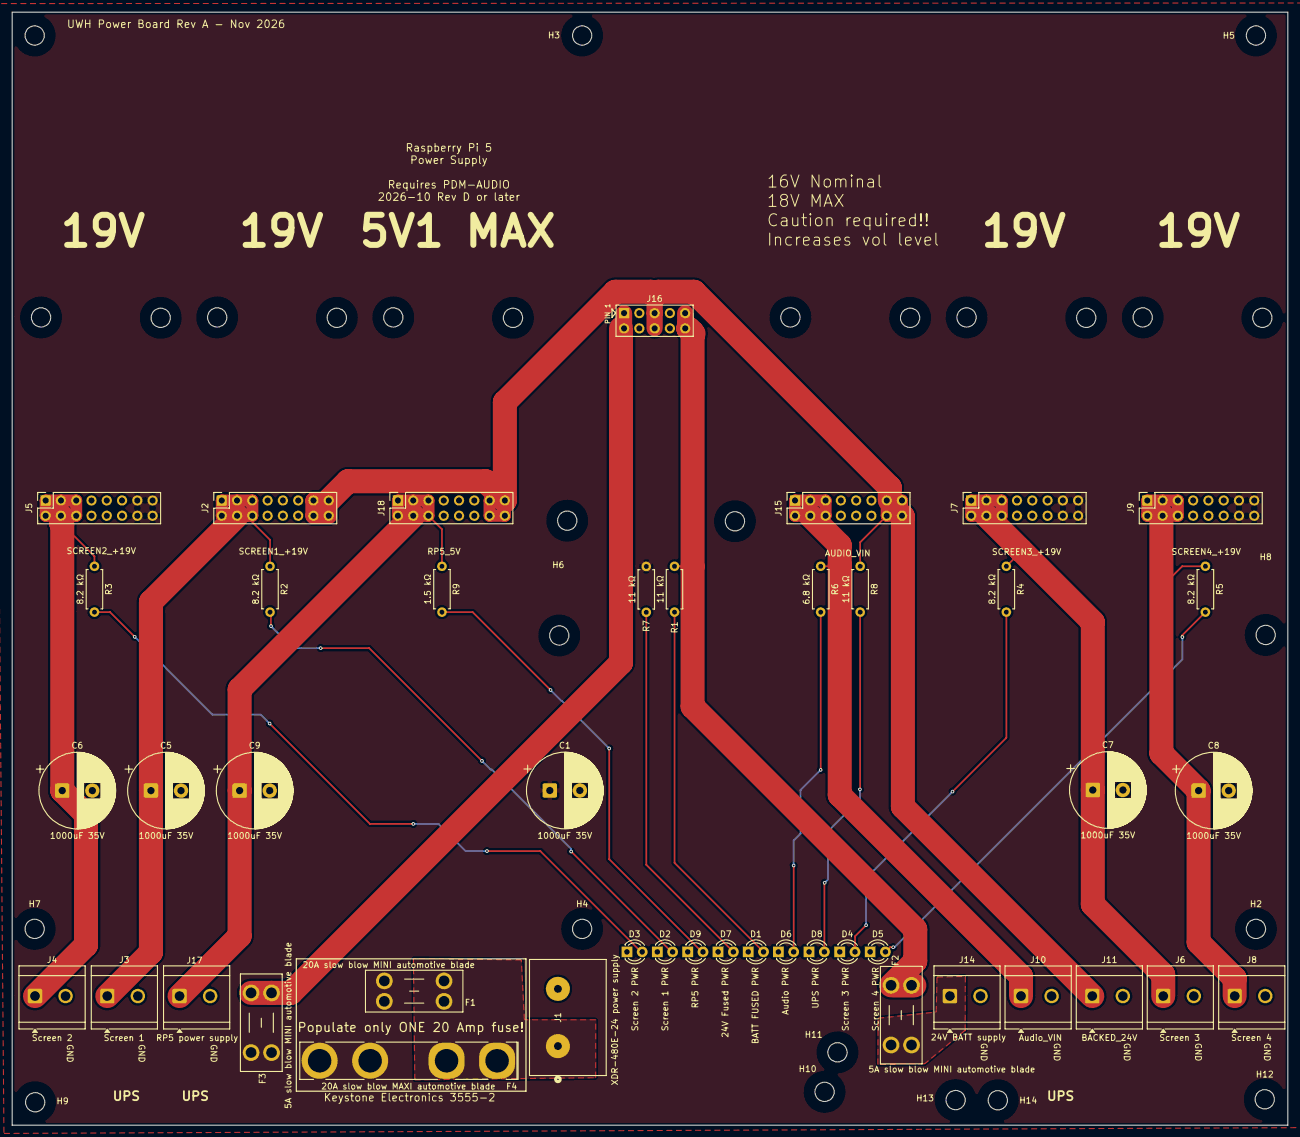
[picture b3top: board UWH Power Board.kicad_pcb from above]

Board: 2 copper layers, 212.0 x 185.0 mm, 58 parts (0 on the bottom side), 22 nets.

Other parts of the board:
H1, H2, H3, H4, H5, H6, H7, H8: MountingHole; MountingHole_3.2mm_M3_Clearance7.2mm
